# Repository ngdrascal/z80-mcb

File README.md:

# Space-Time Productions Master Control Board

---

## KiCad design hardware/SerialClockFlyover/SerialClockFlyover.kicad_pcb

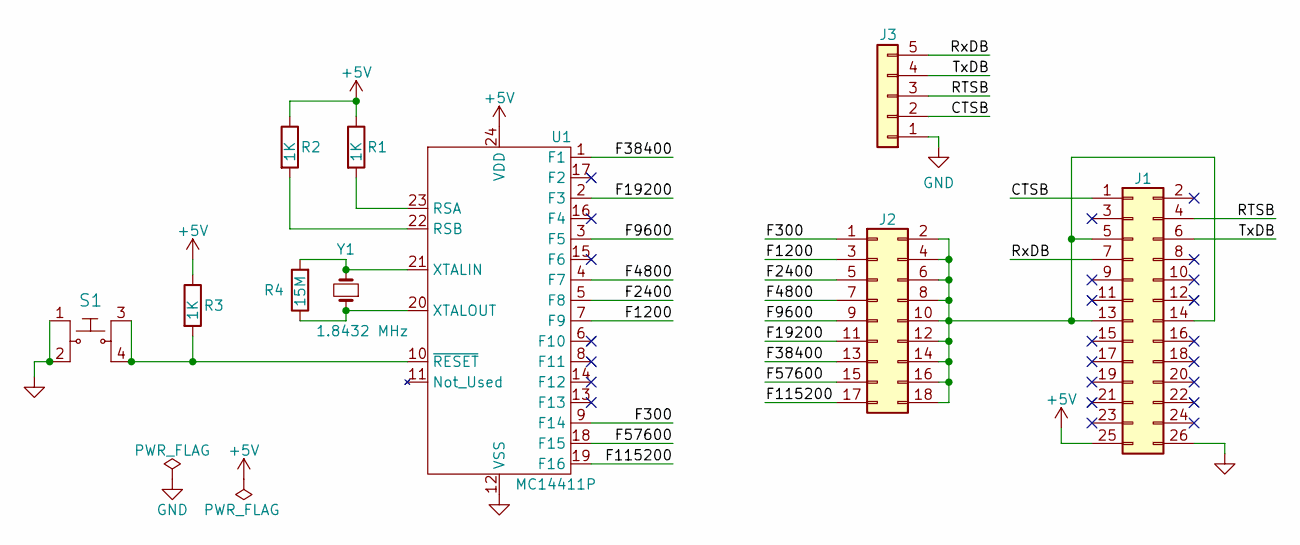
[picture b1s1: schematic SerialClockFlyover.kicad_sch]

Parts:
J1: Conn_02x13_Odd_Even; PinSocket_2x13_P2.54mm_Vertical
J2: Conn_02x09_Odd_Even; PinHeader_2x09_P2.54mm_Vertical
J3: Conn_01x05; PinHeader_1x05_P2.54mm_Vertical
R1, R2, R3: 1K; R_Axial_DIN0207_L6.3mm_D2.5mm_P10.16mm_Horizontal
R4: 15M; R_Axial_DIN0207_L6.3mm_D2.5mm_P10.16mm_Horizontal
S1: 1825910-6; Switch_Tactile_THT_6x6mm; MPN 1825910-6; Digi-Key_PN 450-1650-ND
U1: MC14411P; DIP-24_W15.24mm_Socket
Y1: 1.8432 MHz; Crystal_HC18-U_Vertical

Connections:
+5V: J1.25, R1.1, R2.1, R3.1, U1.24 (VDD)
/CTSB: J1.1, J3.2
/F300: J2.1, U1.9 (F14)
/F1200: J2.3, U1.7 (F9)
/F2400: J2.5, U1.5 (F8)
/F4800: J2.7, U1.4 (F7)
/F9600: J2.9, U1.3 (F5)
/F19200: J2.11, U1.2 (F3)
/F38400: J2.13, U1.1 (F1)
/F57600: J2.15, U1.18 (F15)
/F115200: J2.17, U1.19 (F16)
/RTSB: J1.4, J3.3
/RxDB: J1.7, J3.5
/TxDB: J1.6, J3.4
GND: J1.26, J3.1, S1.1, S1.2, U1.12 (VSS)
unnamed: J1.5, J1.13, J1.14, J2.2, J2.4, J2.6, J2.8, J2.10, J2.12, J2.14, J2.16, J2.18
unnamed: R1.2, U1.23 (RSA)
unnamed: R2.2, U1.22 (RSB)
unnamed: R3.2, S1.3, S1.4, U1.10 (~RESET)
unnamed: R4.1, U1.20 (XTALOUT), Y1.1
unnamed: R4.2, U1.21 (XTALIN), Y1.2

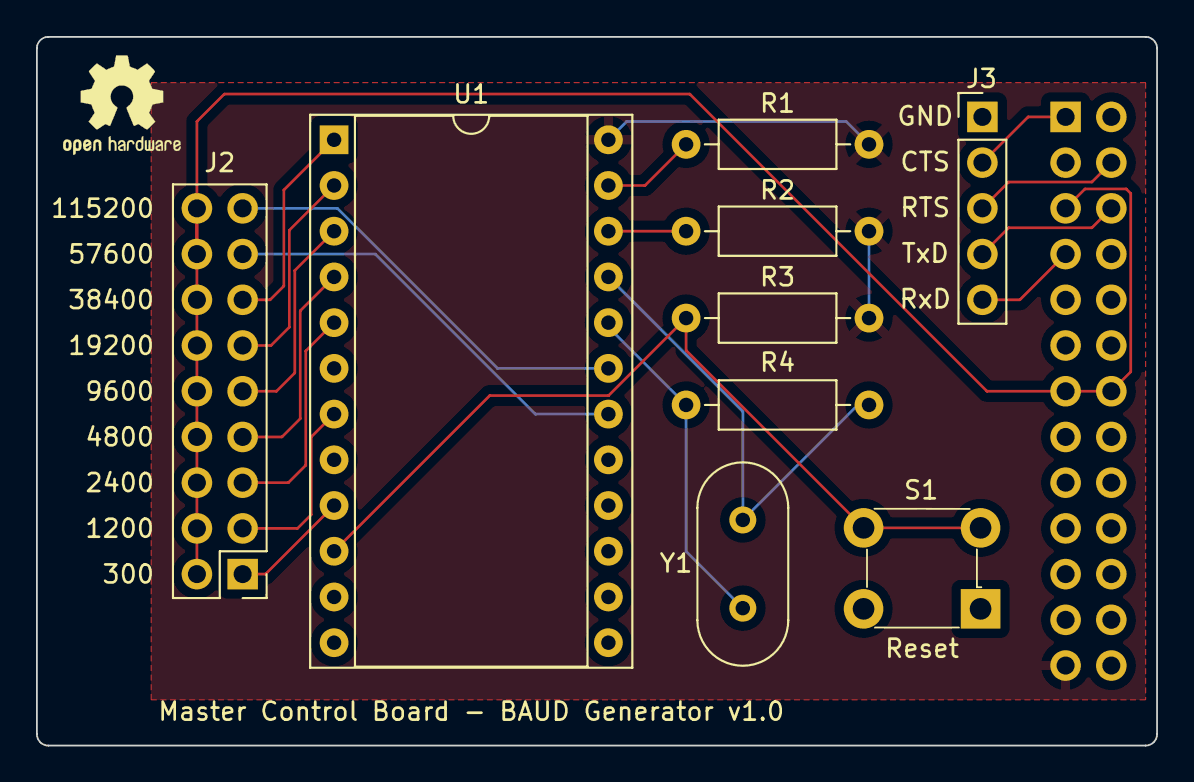
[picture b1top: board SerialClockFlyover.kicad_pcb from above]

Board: 2 copper layers, 62.2 x 39.4 mm, 10 parts (1 on the bottom side), 21 nets.

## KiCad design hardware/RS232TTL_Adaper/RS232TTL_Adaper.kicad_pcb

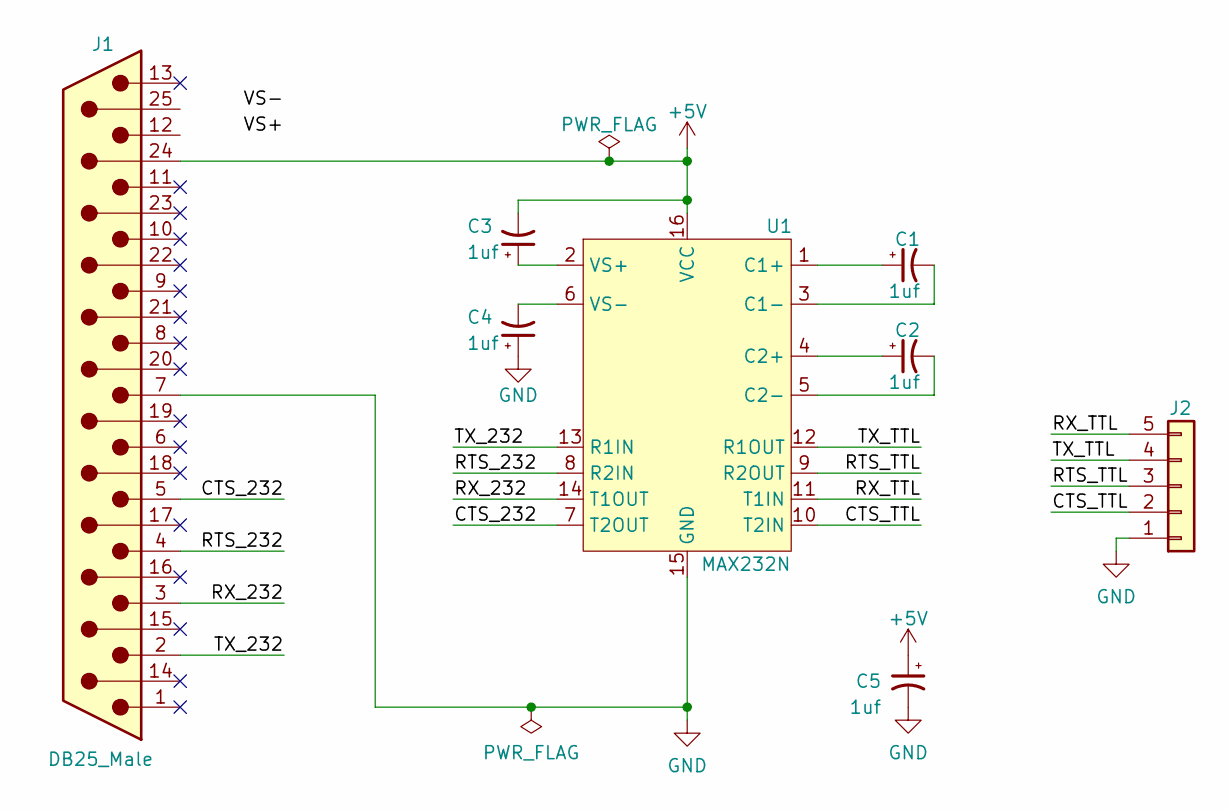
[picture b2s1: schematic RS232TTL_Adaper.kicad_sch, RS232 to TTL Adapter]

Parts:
C1, C2, C3, C4, C5: 1uf; CP_Radial_D5.0mm_P2.00mm
J1: DB25_Male; DSUB-25_Male_Horizontal_P2.77x2.84mm_EdgePinOffset9.40mm
J2: Conn_01x05; PinHeader_1x05_P2.54mm_Vertical
U1: MAX232N; DIP-16_W7.62mm

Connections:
+5V: C3.2, C5.1, J1.24, U1.16 (VCC)
/CTS_232: J1.5, U1.7 (T2OUT)
/CTS_TTL: J2.2, U1.10 (T2IN)
/RTS_232: J1.4, U1.8 (R2IN)
/RTS_TTL: J2.3, U1.9 (R2OUT)
/RX_232: J1.3, U1.14 (T1OUT)
/RX_TTL: J2.5, U1.11 (T1IN)
/TX_232: J1.2, U1.13 (R1IN)
/TX_TTL: J2.4, U1.12 (R1OUT)
GND: C4.1, C5.2, J1.7, J2.1, U1.15 (GND)
unnamed: C1.1, U1.1 (C1+)
unnamed: C1.2, U1.3 (C1-)
unnamed: C2.1, U1.4 (C2+)
unnamed: C2.2, U1.5 (C2-)
unnamed: C3.1, U1.2 (VS+)
unnamed: C4.2, U1.6 (VS-)

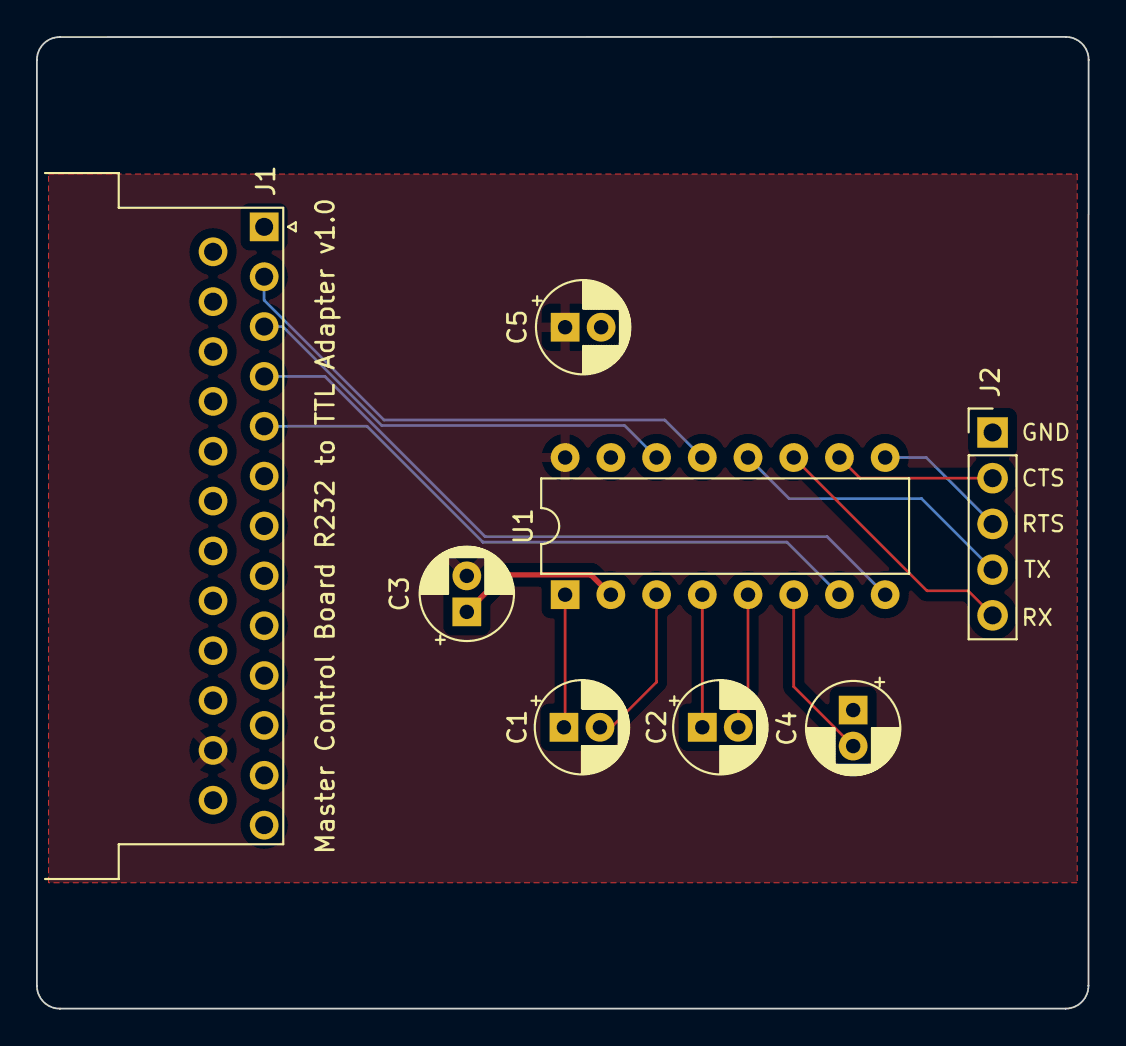
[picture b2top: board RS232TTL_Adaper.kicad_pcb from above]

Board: 2 copper layers, 58.4 x 54.0 mm, 8 parts (0 on the bottom side), 16 nets.

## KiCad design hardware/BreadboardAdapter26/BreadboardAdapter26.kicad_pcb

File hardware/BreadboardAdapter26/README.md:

# Breadboard adapter for 26 pin headers

---

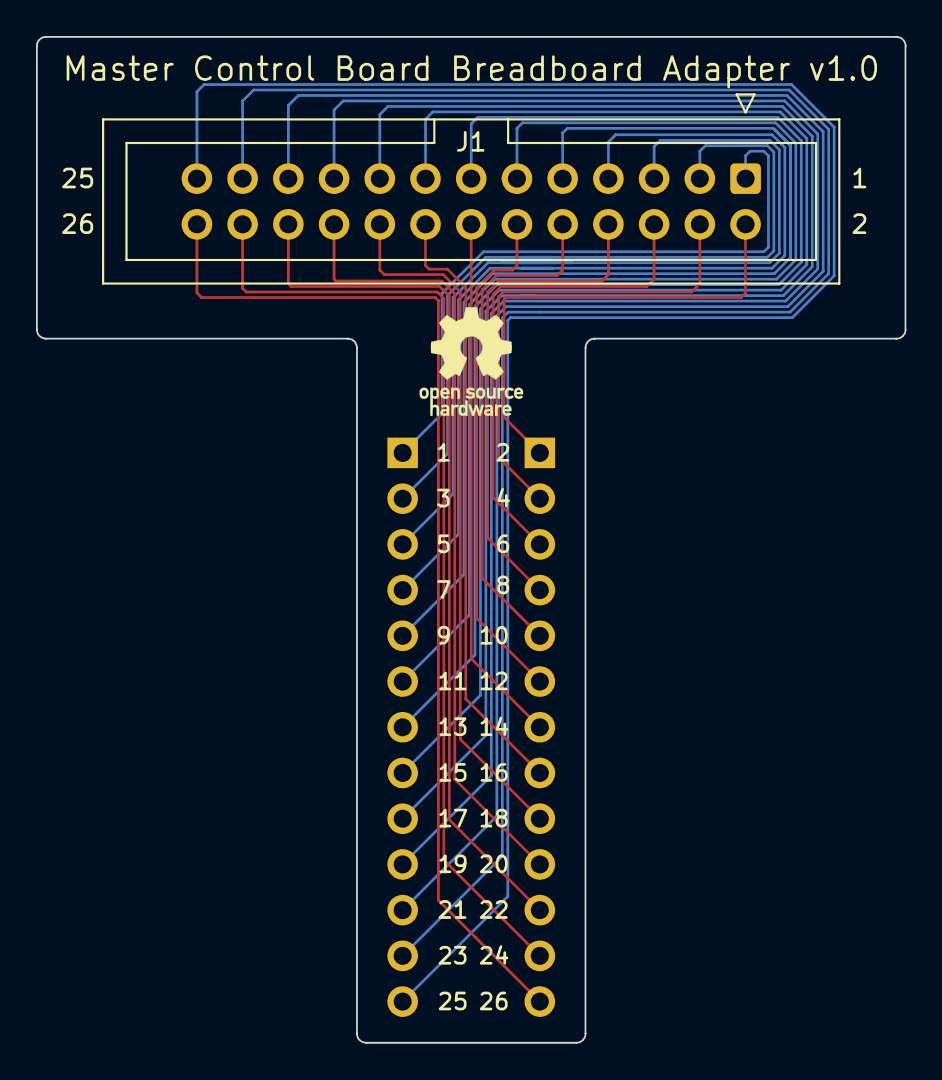
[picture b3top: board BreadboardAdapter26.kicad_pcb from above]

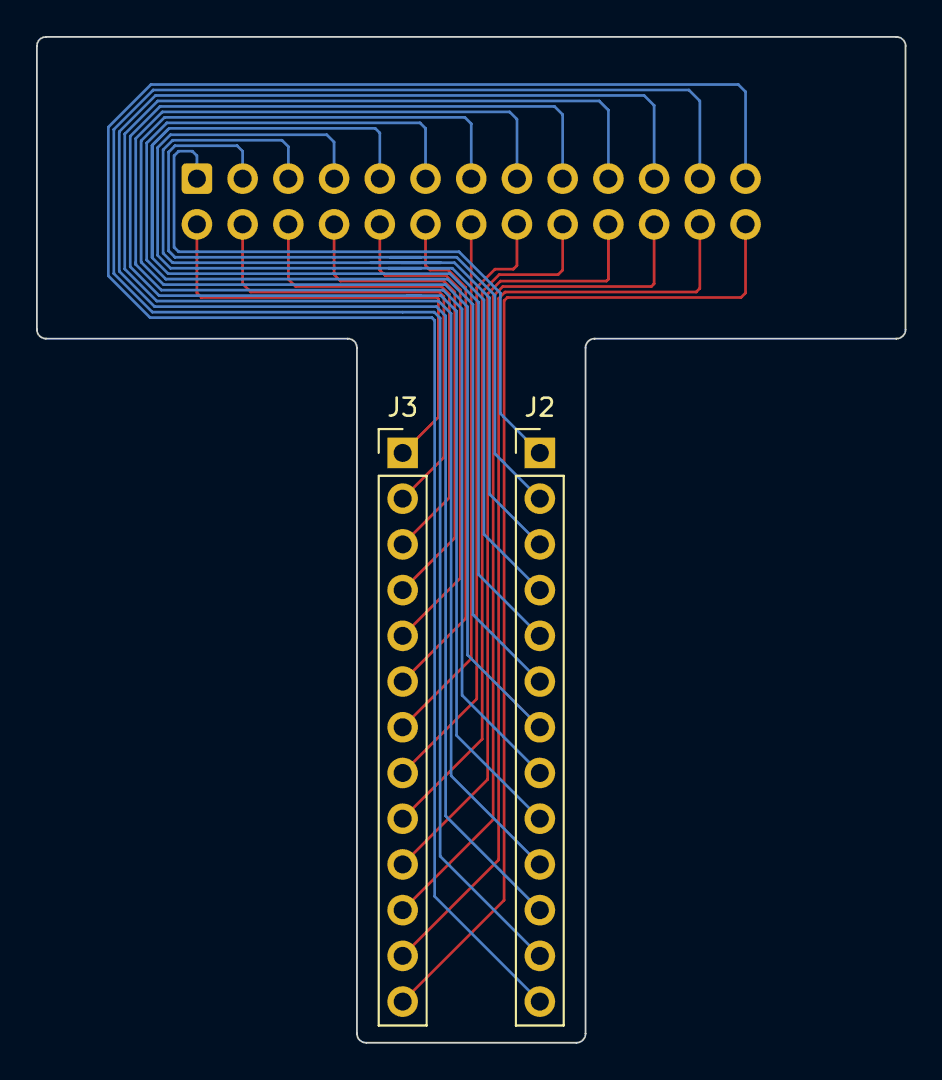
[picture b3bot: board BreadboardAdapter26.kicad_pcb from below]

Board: 2 copper layers, 48.3 x 55.9 mm, 3 parts (2 on the bottom side), 26 nets.

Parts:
J1: Conn_02x13_Odd_Even; IDC-Header_2x13_P2.54mm_Vertical
J2, J3: Conn_01x13; PinHeader_1x13_P2.54mm_Vertical

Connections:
unnamed: J1.1, J2.1
unnamed: J1.2, J3.1
unnamed: J1.3, J2.2
unnamed: J1.4, J3.2
unnamed: J1.5, J2.3
unnamed: J1.6, J3.3
unnamed: J1.7, J2.4
unnamed: J1.8, J3.4
unnamed: J1.9, J2.5
unnamed: J1.10, J3.5
unnamed: J1.11, J2.6
unnamed: J1.12, J3.6
unnamed: J1.13, J2.7
unnamed: J1.14, J3.7
unnamed: J1.15, J2.8
unnamed: J1.16, J3.8
unnamed: J1.17, J2.9
unnamed: J1.18, J3.9
unnamed: J1.19, J2.10
unnamed: J1.20, J3.10
unnamed: J1.21, J2.11
unnamed: J1.22, J3.11
unnamed: J1.23, J2.12
unnamed: J1.24, J3.12
unnamed: J1.25, J2.13
unnamed: J1.26, J3.13

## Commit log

2021-12-04 added schema pdf
2021-12-04 added picture
2022-01-25 added TinyBasic source - unmodified from cpuville
2022-01-26 ignore build specific stuff
2022-01-26 first working version
2022-01-26 added build instructions
2022-01-26 relocate instructions
2022-01-26 added chip specific tests
2022-01-27 added .hex output files
2022-01-27 moved all tools to a separate dir
2022-01-28 formatting changes only
2022-01-28 original version from Jowel Owens
2022-01-28 updated to z80 mnemonics
2022-01-29 added datassheets
2022-01-31 rename to reflect its purpose
2022-02-01 renamed to keep original
2022-02-01 adding source
2022-02-01 added my header
2022-02-01 change SIO to port B
2022-02-03 added header
2022-02-03 update labels
2022-02-04 standardize style & formatting
2022-02-04 added missing label
2022-02-04 initial checkin
2022-02-05 ignore output from the simulator
2022-02-05 fixed backspacing
2022-02-05 Print welcome msg
2022-02-07 added SioStatus and PrintString routines
2022-02-09 reorganized data declarations
2022-02-09 removed unused code
2022-02-10 add byte <-> hex conversions
2022-02-13 ignore DeZog files
2022-02-13 add configuration for DeZog simulator
2022-02-13 set default task
2022-02-13 added DumpRange processing
2022-02-13 code formatting/reording
2022-02-13 added word <-> hex conversions
2022-02-13 completed DumpRange processing
2022-02-14 work around for ROM emulator
2022-02-19 Adding Gerber Files
2022-02-19 additional datasheet
2022-02-19 remove zip add Gerber files
2022-02-19 stop tracking .zip files
2022-02-19 fix location of pcb graphics
2022-02-19 add documentation
2022-02-19 added readme
2022-02-19 cleanup list of ignored files
2022-02-19 stop tracking .kicad_prl files
2022-02-19 reorg symbol files
2022-02-20 moved graphics
2022-02-20 added image of back
2022-02-22 added MC14411P
2022-02-24 remove connection to +/- 12v
2022-03-02 add Gerber files
2022-03-02 added 15M resistor
2022-03-02 add more excludes
2022-03-02 added table mapping clock freq. to Baud rates
2022-03-07 make it easier to switch between A and B channels
2022-03-13 switched to A channel
2022-03-13 switched to SIO A channel
2022-03-13 changed to SIO A channel
2022-03-13 added scans of remaining original documents
2022-03-15 added OSHW logo
2023-12-27 add monitor v5
